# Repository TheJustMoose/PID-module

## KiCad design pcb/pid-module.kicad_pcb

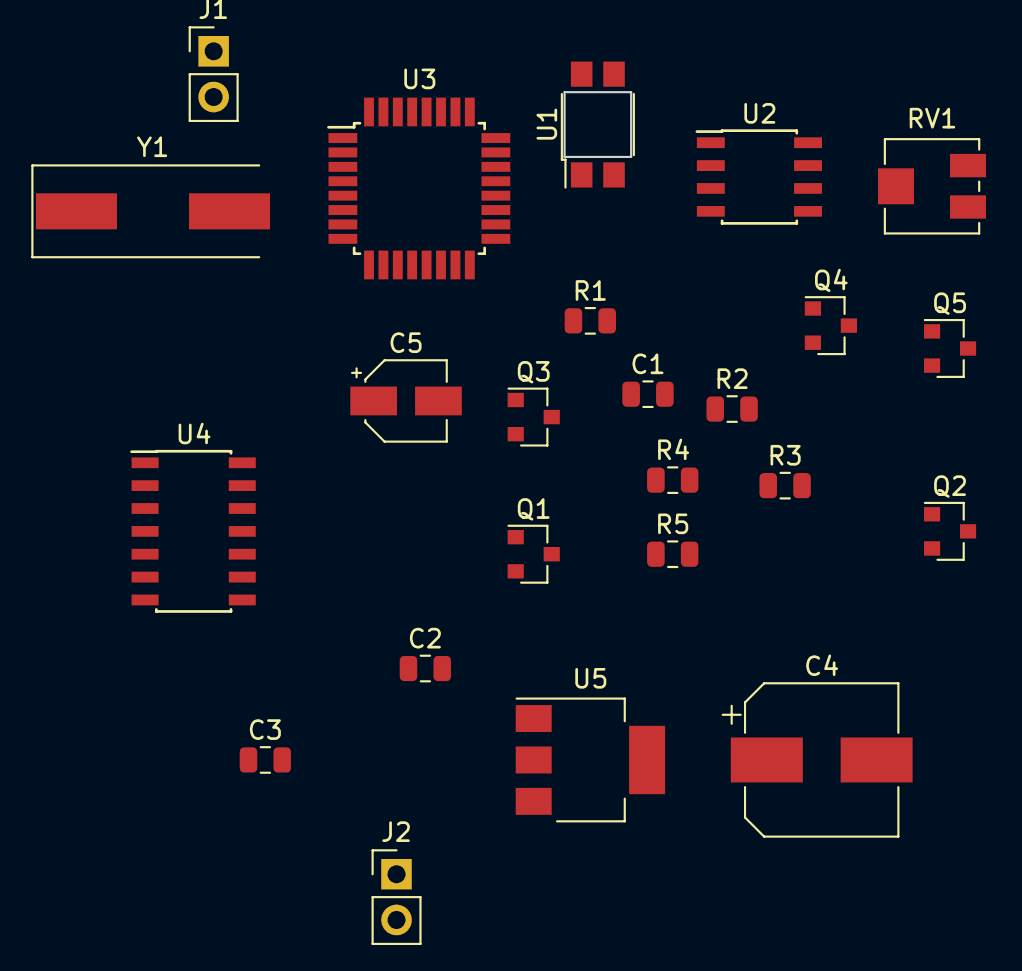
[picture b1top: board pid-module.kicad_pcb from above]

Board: 2 copper layers, 24 parts (0 on the bottom side), 21 nets, no tracks yet.

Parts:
C1: 100n; C_0805_2012Metric
C2, C3: C_Small; C_0805_2012Metric
C4: CP; CP_Elec_8x5.4
C5: CP; CP_Elec_4x3
J1: UART; PinHeader_1x02_P2.54mm_Vertical
J2: Conn_01x02_Male; PinHeader_1x02_P2.54mm_Vertical
Q1, Q3, Q5: IRLML6402; SOT-23
Q2, Q4: IRLML2502; SOT-23
R1: 1k; R_0805_2012Metric
R2, R3: 4.7k; R_0805_2012Metric
R4: 50k; R_0805_2012Metric
R5: 10k; R_0805_2012Metric
RV1: 10k; Potentiometer_Vishay_TS53YJ_Vertical
U1: ITR8307; Everlight_ITR8307
U2: LM311; SOIC-8_3.9x4.9mm_P1.27mm
U3: ATmega88PA-AU; TQFP-32_7x7mm_P0.8mm
U4: 74LS27; SOIC-14_3.9x8.7mm_P1.27mm
U5: AMS1117-5.0; SOT-223-3_TabPin2
Y1: Crystal; Crystal_SMD_HC49-SD

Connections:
/M-: Q1.1, U3.11, U4.1, U4.9
/PWM: U3.13, U4.4, U4.10
GND: C1.2, C2.2, C3.2, C4.2, C5.2, Q2.2, Q4.2, Q5.1, R5.2, RV1.3, U1.1, U1.4, U2.1, U2.4, U3.3, U3.5, U3.21, U4.7, U4.13, U5.1
unnamed: C1.1, R4.2, R5.1, U3.23
unnamed: C2.1, U3.8, Y1.2
unnamed: C3.1, U3.7, Y1.1
unnamed: C4.1, R1.1, R2.1, R3.1, RV1.1, U2.8, U3.4, U3.6, U3.18, U4.14, U5.2
unnamed: C5.1, Q1.2, Q3.2, Q5.2, R4.1, U5.3
unnamed: J1.1, U3.31
unnamed: J1.2, U3.30
unnamed: J2.1, Q1.3, Q2.3
unnamed: J2.2, Q3.3, Q4.3
unnamed: Q2.1, U4.6
unnamed: Q3.1, U3.10, U4.2, U4.5
unnamed: Q4.1, U4.8
unnamed: R1.2, U1.2
unnamed: R2.2, U1.3, U2.2
unnamed: R3.2, U2.7, U3.12
unnamed: RV1.2, U2.3
unnamed: U2.5, U2.6
unnamed: U4.3, U4.11, U4.12

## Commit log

2018-11-21 Add KiCAD circuits
